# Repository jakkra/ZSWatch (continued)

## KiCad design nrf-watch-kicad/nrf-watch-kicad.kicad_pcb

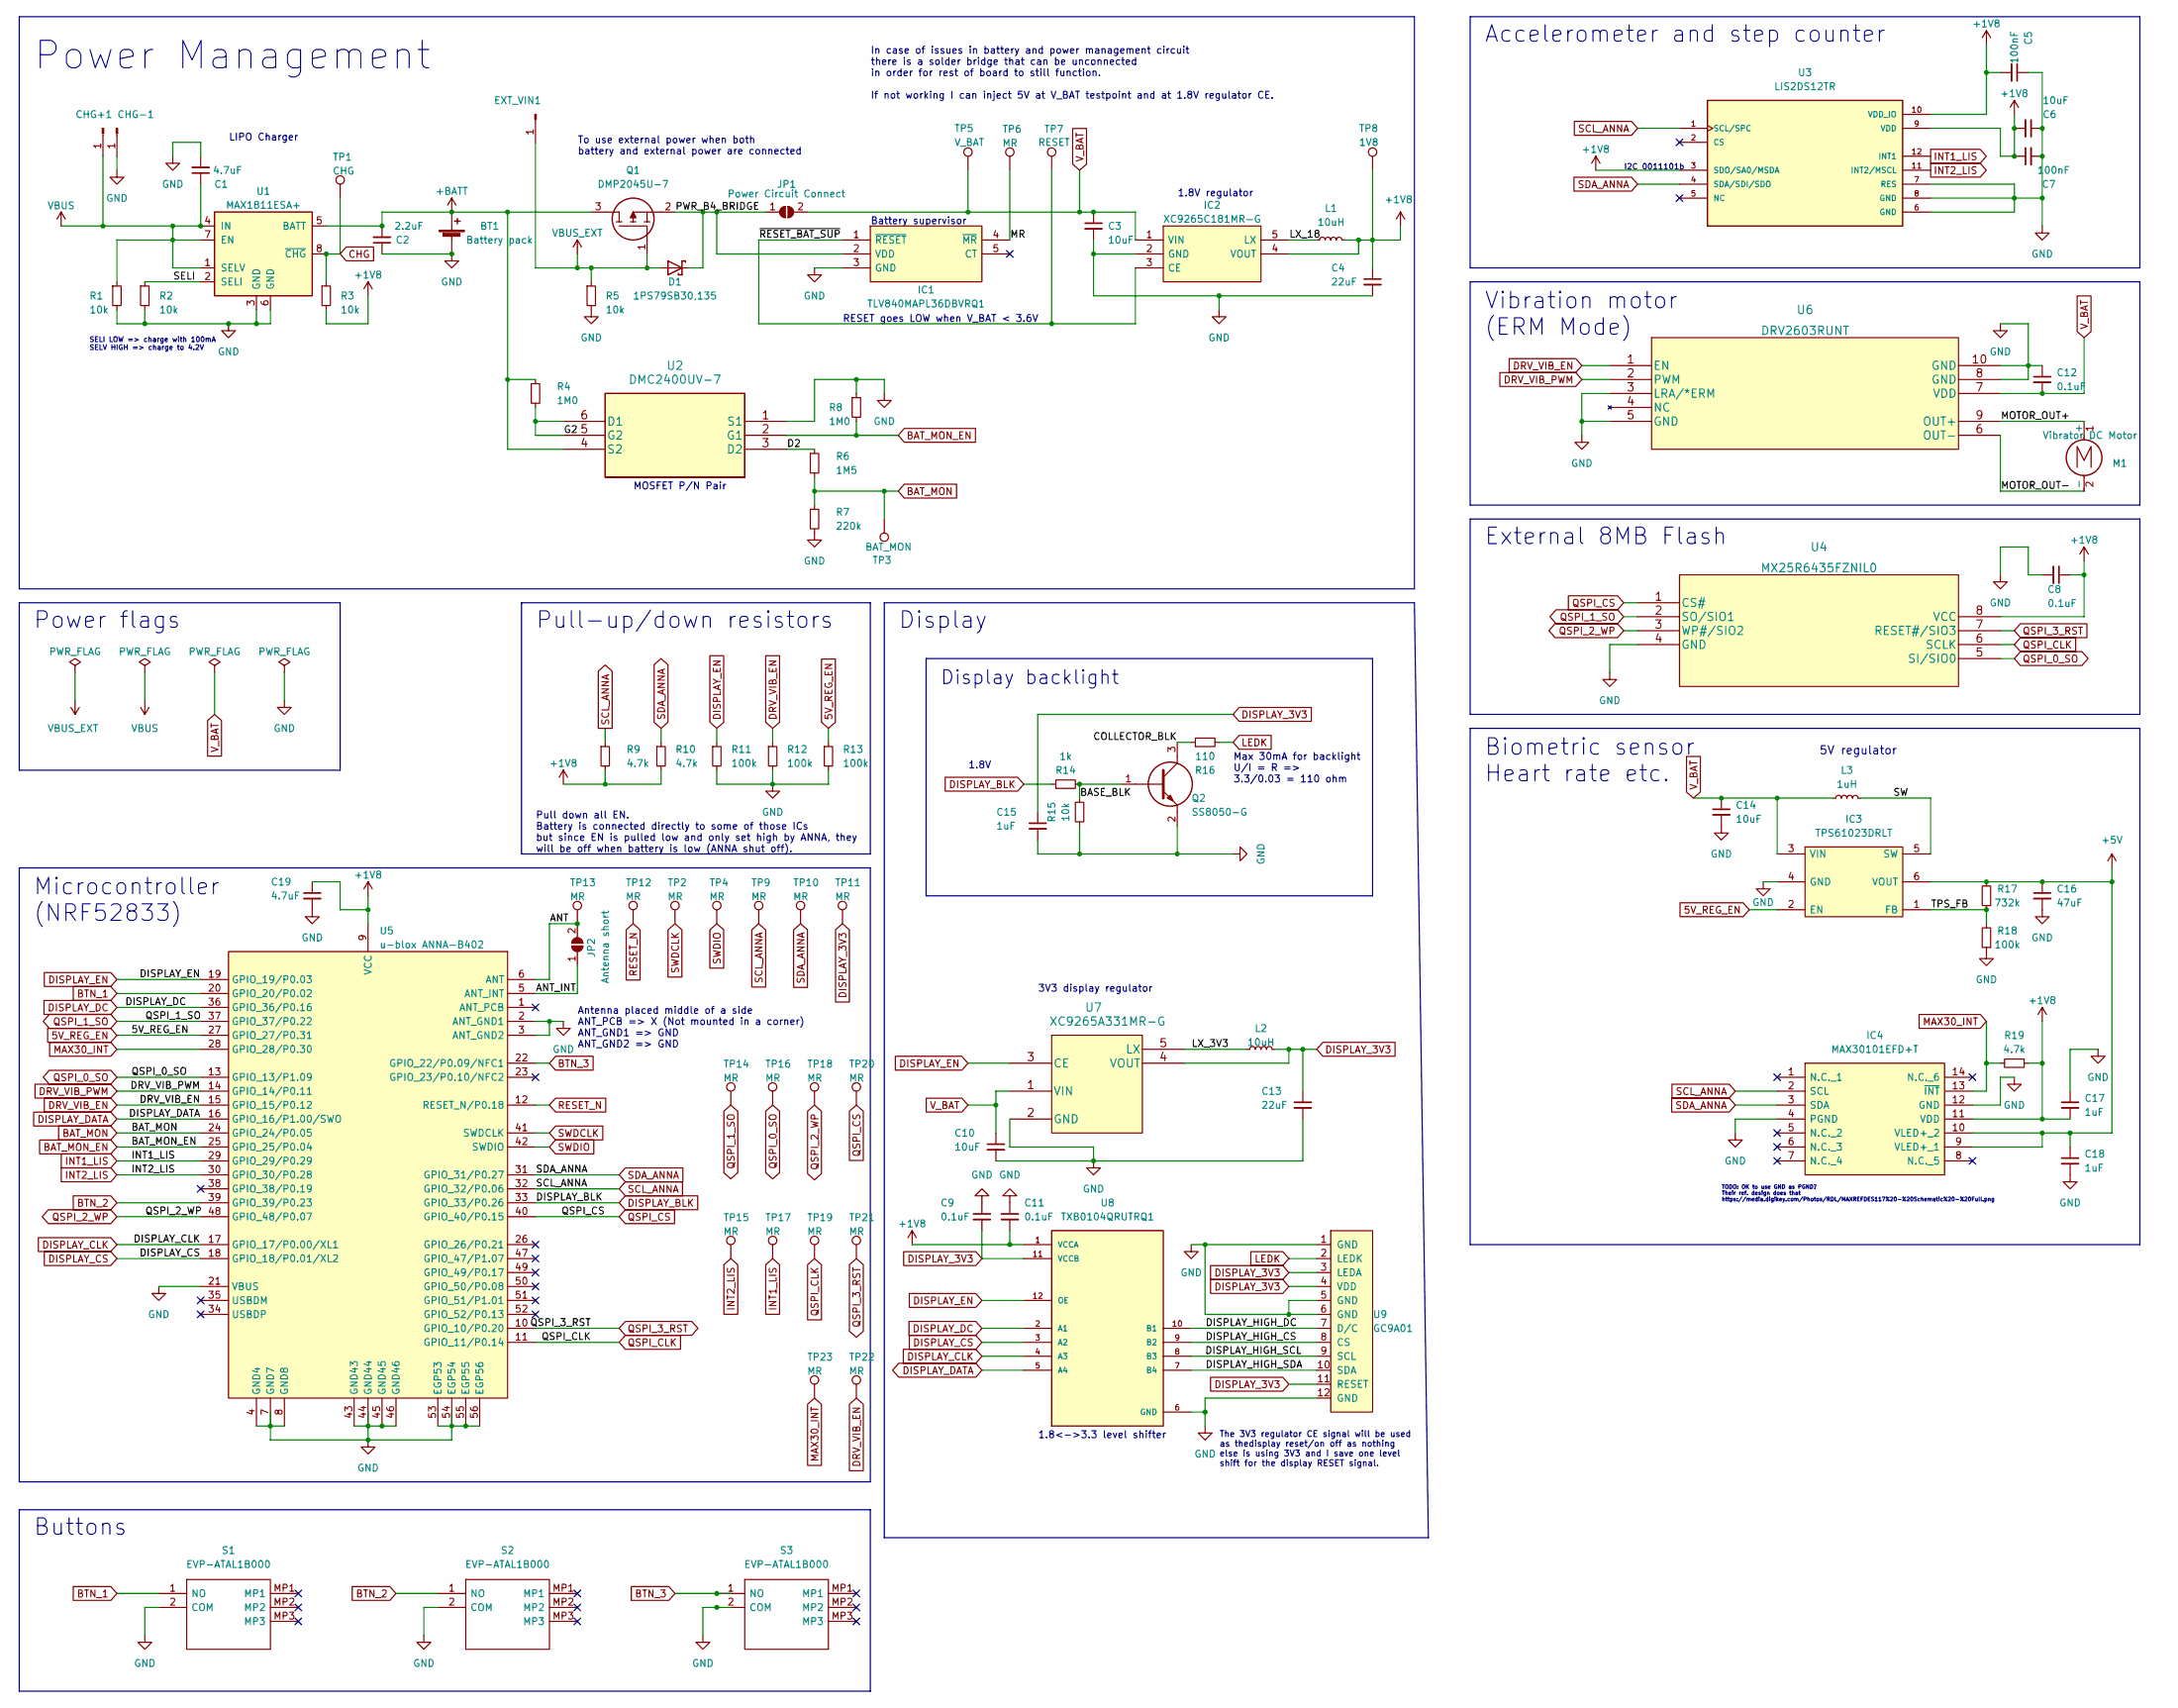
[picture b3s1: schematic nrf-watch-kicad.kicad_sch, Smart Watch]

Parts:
BT1: Battery pack; SolderWire-0.1sqmm_1x02_P3.6mm_D0.4mm_OD1mm
C1, C19: 4.7uF; C_0603_1608Metric_Pad1.08x0.95mm_HandSolder
C2: 2.2uF; C_0603_1608Metric_Pad1.08x0.95mm_HandSolder
C3, C6, C10, C14: 10uF; C_0603_1608Metric_Pad1.08x0.95mm_HandSolder
C4, C13: 22uF; C_0603_1608Metric_Pad1.08x0.95mm_HandSolder
C5, C7: 100nF; C_0603_1608Metric_Pad1.08x0.95mm_HandSolder
C8, C9, C11, C12: 0.1uF; C_0603_1608Metric_Pad1.08x0.95mm_HandSolder
C15, C17, C18: 1uF; C_0603_1608Metric_Pad1.08x0.95mm_HandSolder
C16: 47uF; C_0603_1608Metric_Pad1.08x0.95mm_HandSolder
CHG+1: Conn_01x01_Male; TestPoint_Pad_D1.5mm
CHG-1: Conn_01x01_Male; TestPoint_Pad_1.5x1.5mm
D1: 1PS79SB30,135; SOD523
EXT_VIN1: Conn_01x01_Male; TestPoint_Pad_D1.5mm
IC1: TLV840MAPL36DBVRQ1; SOT95P280X145-5N; Mouser Part Number 595-V840MAPL36DBVRQ1
IC2: XC9265C181MR-G; SOT95P280X130-5N; Mouser Part Number 865-XC9265C181MR-G
IC3: TPS61023DRLT; SOTFL50P160X60-6N; Mouser Part Number 595-TPS61023DRLT
IC4: MAX30101EFD+T; 14-LEAD-OESIP; Mouser Part Number 700-MAX30101EFD+T
JP1: Power Circuit Connect; SolderJumper-2_P1.3mm_Open_RoundedPad1.0x1.5mm
JP2: Antenna short; SolderJumper-2_P1.3mm_Open_Pad1.0x1.5mm
L1, L2: 10uH; L_0603_1608Metric_Pad1.05x0.95mm_HandSolder
L3: 1uH; L_0603_1608Metric_Pad1.05x0.95mm_HandSolder
M1: Vibrator DC Motor; TestPoint_2Pads_Pitch2.54mm_Drill0.8mm
Q1: DMP2045U-7; SOT96P240X110-3N; Mouser Part Number 621-DMP2045U-7
Q2: SS8050-G; SOT95P240X115-3N; Mouser Part Number 750-SS8050-G
R1, R2, R3, R5, R15: 10k; R_0603_1608Metric_Pad0.98x0.95mm_HandSolder
R4, R8: 1M0; R_0603_1608Metric_Pad0.98x0.95mm_HandSolder
R6: 1M5; R_0603_1608Metric_Pad0.98x0.95mm_HandSolder
R7: 220k; R_0603_1608Metric_Pad0.98x0.95mm_HandSolder
R9, R10, R19: 4.7k; R_0603_1608Metric_Pad0.98x0.95mm_HandSolder
R11, R12, R13, R18: 100k; R_0603_1608Metric_Pad0.98x0.95mm_HandSolder
R14: 1k; R_0603_1608Metric_Pad0.98x0.95mm_HandSolder
R16: 110; R_0603_1608Metric_Pad0.98x0.95mm_HandSolder
R17: 732k; R_0603_1608Metric_Pad0.98x0.95mm_HandSolder
S1, S2, S3: EVP-ATAL1B000; EVPATAL1B000; Mouser Part Number 667-EVP-ATAL1B000
TP1: CHG; TestPoint_Pad_D1.0mm
TP2, TP4, TP6, TP9, TP10, TP11, TP12, TP13: MR; TestPoint_Pad_D1.0mm
TP3: BAT_MON; TestPoint_Pad_D1.0mm
TP5: V_BAT; TestPoint_Pad_D1.0mm
TP7: RESET; TestPoint_Pad_D1.0mm
TP8: 1V8; TestPoint_Pad_D1.0mm
TP14, TP15, TP16, TP17, TP18, TP19, TP20, TP21, TP22, TP23: MR; TestPoint_Pad_D0.4mm
U1: MAX1811ESA+; SOIC127P600X175-8N
U2: DMC2400UV-7
U3: LIS2DS12TR
U4: MX25R6435FZNIL0
U5: u-blox ANNA-B402; ANNA-B402_altium_import
U6: DRV2603RUNT
U7: XC9265A331MR-G; SOT95P280X130-5N
U8: TXB0104QRUTRQ1; HPA01164RUTR; PARTREV 4210580/C 06/12
U9: GC9A01; GC9A01_disp

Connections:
5V_REG_EN: IC3.2 (EN), R13.1, U5.27 (GPIO_27/P0.31)
+1V8: C4.1, C5.2, C6.2, C7.1, C8.1, C11.2, C17.2, C19.1, IC2.4 (VOUT), IC4.11 (VDD), L1.2, R3.2, R9.2, R10.2, R19.1, TP8.1, U3.3 (SDO/SA0/MSDA), U3.9 (VDD), U3.10 (VDD_IO), U4.8 (VCC), U5.9 (VCC), U8.1 (VCCA)
+5V: C16.1, C18.1, IC3.6 (VOUT), IC4.9 (VLED+_1), IC4.10 (VLED+_2), R17.2
+BATT: BT1.1 (+), C2.2, Q1.3, R4.1, U1.5 (BATT), U2.4 (S2)
/ANT: JP2.2 (B), TP13.1, U5.6 (ANT)
/ANT_INT: JP2.1 (A), U5.5 (ANT_INT)
/BASE_BLK: Q2.1, R14.2, R15.1
/COLLECTOR_BLK: Q2.3, R16.1
/D2: R6.1, U2.3 (D2)
/DISPLAY_HIGH_CS: U8.9 (B2), U9.8 (CS)
/DISPLAY_HIGH_DC: U8.10 (B1), U9.7 (D/C)
/DISPLAY_HIGH_SCL: U8.8 (B3), U9.9 (SCL)
/DISPLAY_HIGH_SDA: U8.7 (B4), U9.10 (SDA)
/G2: R4.2, U2.5 (G2), U2.6 (D1)
/LX_3V3: L2.1, U7.5 (LX)
/LX_18: IC2.5 (LX), L1.1
/MOTOR_OUT+: M1.1 (+), U6.9 (OUT+)
/MOTOR_OUT-: M1.2 (-), U6.6 (OUT-)
/MR: IC1.4 (~MR), TP6.1
/PWR_B4_BRIDGE: D1.1, IC1.2 (VDD), JP1.1 (A), Q1.2
/SELI: R2.1, U1.2 (SELI)
/SW: IC3.5 (SW), L3.2
/TPS_FB: IC3.1 (FB), R17.1, R18.2
/~RESET_BAT_SUP: IC1.1 (~RESET), IC2.3 (CE), TP7.1
BAT_MON: R6.2, R7.1, TP3.1, U5.24 (GPIO_24/P0.05)
BAT_MON_EN: R8.2, U2.2 (G1), U5.25 (GPIO_25/P0.04)
BTN_1: S1.1 (NO), U5.20 (GPIO_20/P0.02)
BTN_2: S2.1 (NO), U5.39 (GPIO_39/P0.23)
BTN_3: S3.1 (NO), U5.22 (GPIO_22/P0.09/NFC1)
CHG: R3.1, TP1.1, U1.8 (~CHG)
DISPLAY_3V3: C9.2, C13.1, C15.1, L2.2, TP11.1, U7.4 (VOUT), U8.11 (VCCB), U9.3 (LEDA), U9.4 (VDD), U9.11 (RESET)
DISPLAY_BLK: R14.1, U5.33 (GPIO_33/P0.26)
DISPLAY_CLK: U5.17 (GPIO_17/P0.00/XL1), U8.4 (A3)
DISPLAY_CS: U5.18 (GPIO_18/P0.01/XL2), U8.3 (A2)
DISPLAY_DATA: U5.16 (GPIO_16/P1.00/SWO), U8.5 (A4)
DISPLAY_DC: U5.36 (GPIO_36/P0.16), U8.2 (A1)
DISPLAY_EN: R11.1, U5.19 (GPIO_19/P0.03), U7.3 (CE), U8.12 (OE)
DRV_VIB_EN: R12.1, TP22.1, U5.15 (GPIO_15/P0.12), U6.1 (EN)
DRV_VIB_PWM: U5.14 (GPIO_14/P0.11), U6.2 (PWM)
GND: BT1.2 (-), C1.2, C2.1, C3.2, C4.2, C5.1, C6.1, C7.2, C8.2, C9.1, C10.2, C11.1, C12.1, C13.2, C14.2, C15.2, C16.2, C17.1, C18.2, C19.2, CHG-1.1, IC1.3 (GND), IC2.2 (GND), IC3.4 (GND), IC4.4 (PGND), IC4.12 (GND), Q2.2, R1.2, R2.2, R5.2, R7.2, R8.1, R11.2, R12.2, R13.2, R15.2, R18.1, S1.2 (COM), S2.2 (COM), S3.2 (COM), U1.3 (GND), U1.6 (GND), U2.1 (S1), U3.6 (GND), U3.7 (RES), U3.8 (GND), U4.4 (GND), U5.2 (ANT_GND1), U5.3 (ANT_GND2), U5.4 (GND4), U5.7 (GND7), U5.8 (GND8), U5.21 (VBUS), U5.43 (GND43), U5.44 (GND44), U5.45 (GND45), U5.46 (GND46), U5.53 (EGP53), U5.54 (EGP54), U5.55 (EGP55), U5.56 (EGP56), U6.3 (LRA/*ERM), U6.5 (GND), U6.8 (GND), U6.10 (GND), U7.2 (GND), U8.6 (GND), U9.1 (GND), U9.5 (GND), U9.6 (GND), U9.12 (GND)
INT1_LIS: TP17.1, U3.12 (INT1), U5.29 (GPIO_29/P0.29)
INT2_LIS: TP15.1, U3.11 (INT2/MSCL), U5.30 (GPIO_30/P0.28)
LEDK: R16.2, U9.2 (LEDK)
MAX30_INT: IC4.13 (~INT), R19.2, TP23.1, U5.28 (GPIO_28/P0.30)
QSPI_0_SO: TP16.1, U4.5 (SI/SIO0), U5.13 (GPIO_13/P1.09)
QSPI_1_SO: TP14.1, U4.2 (SO/SIO1), U5.37 (GPIO_37/P0.22)
QSPI_2_WP: TP18.1, U4.3 (WP#/SIO2), U5.48 (GPIO_48/P0.07)
QSPI_3_RST: TP21.1, U4.7 (RESET#/SIO3), U5.10 (GPIO_10/P0.20)
QSPI_CLK: TP19.1, U4.6 (SCLK), U5.11 (GPIO_11/P0.14)
QSPI_CS: TP20.1, U4.1 (CS#), U5.40 (GPIO_40/P0.15)
RESET_N: TP12.1, U5.12 (RESET_N/P0.18)
SCL_ANNA: IC4.2 (SCL), R9.1, TP9.1, U3.1 (SCL/SPC), U5.32 (GPIO_32/P0.06)
SDA_ANNA: IC4.3 (SDA), R10.1, TP10.1, U3.4 (SDA/SDI/SDO), U5.31 (GPIO_31/P0.27)
SWDCLK: TP2.1, U5.41 (SWDCLK)
SWDIO: TP4.1, U5.42 (SWDIO)
VBUS: C1.1, CHG+1.1, R1.1, U1.1 (SELV), U1.4 (IN), U1.7 (EN)
VDDA: D1.2, EXT_VIN1.1, Q1.1, R5.1
V_BAT: C3.1, C10.1, C12.2, C14.1, IC2.1 (VIN), IC3.3 (VIN), JP1.2 (B), L3.1, TP5.1, U6.7 (VDD), U7.1 (VIN)

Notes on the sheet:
Display backlight
Biometric sensor Heart rate etc.
Antenna placed middle of a side ANT_PCB => X (Not mounted in a corner) ANT_GND1 => GND ANT_GND2 => GND
Microcontroller (NRF52833)
3V3 display regulator
Pull-up/down resistors
MOSFET P/N Pair
Power Management
SELI LOW => charge with 100mA SELV HIGH => charge to 4.2V
Battery supervisor
RESET goes LOW when V_BAT < 3.6V
Buttons
TODO: OK to use GND as PGND? Their ref. design does that https://media.digikey.com/Photos/RDL/MAXREFDES117%20-%20Schematic%20-%20Full.png
Max 30mA for backlight U/I = R => 3.3/0.03 = 110 ohm
In case of issues in battery and power management circuit there is a solder bridge that can be unconnected in order for rest of board to still function. If not working I can inject 5V at V_BAT testpoint and at 1.8V regulator CE.
Power flags
To use external power when both battery and external power are connected
External 8MB Flash
Pull down all EN. Battery is connected directly to some of those ICs but since EN is pulled low and only set high by ANNA, they will be off when battery is low (ANNA shut off).
Accelerometer and step counter
LIPO Charger
_{I2C 0011101b}
5V regulator
1.8<->3.3 level shifter
The 3V3 regulator CE signal will be used as thedisplay reset/on off as nothing else is using 3V3 and I save one level shift for the display RESET signal.
Vibration motor (ERM Mode)
Display
1.8V regulator
1.8V

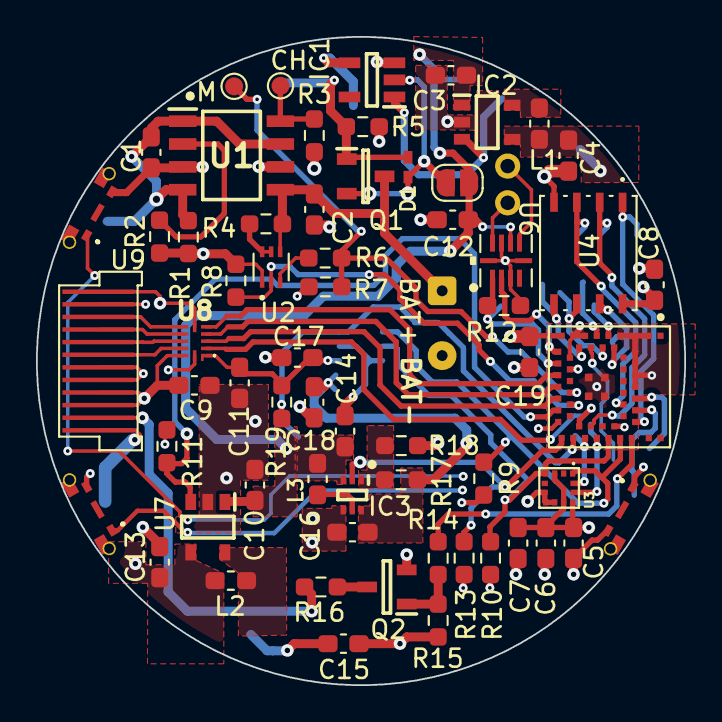
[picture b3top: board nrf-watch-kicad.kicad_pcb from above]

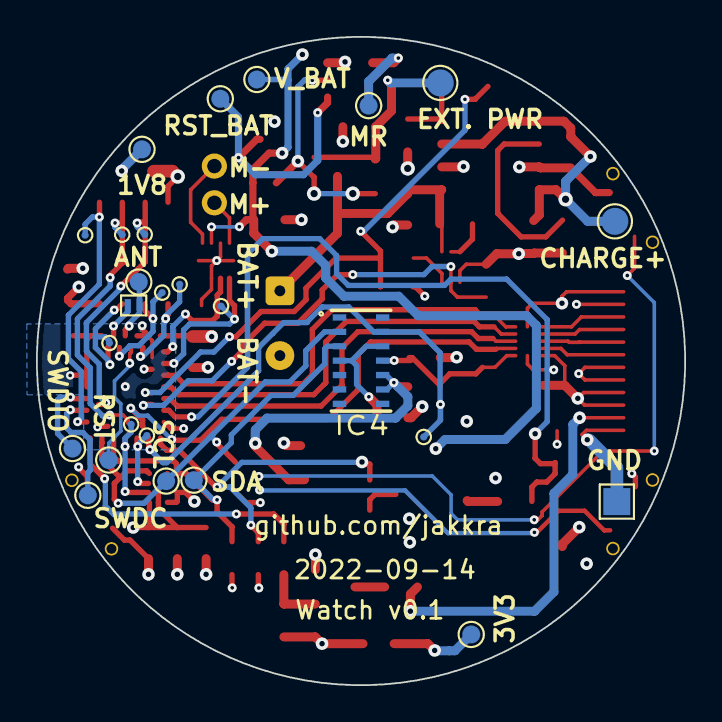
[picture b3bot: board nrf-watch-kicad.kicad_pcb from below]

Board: 4 copper layers, 36.0 x 36.0 mm, 90 parts (26 on the bottom side), 58 nets.

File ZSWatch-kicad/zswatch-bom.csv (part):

Source:,G:\projects\watch\ZSWatch-kicad\nrf-watch-kicad.kicad_sch,,,,,,,,,,,,,,,,,,,,,,,,,
Date:,1/16/2023 8:22:16 AM,,,,,,,,,,,,,,,,,,,,,,,,,
Tool:,Eeschema (6.0.7),,,,,,,,,,,,,,,,,,,,,,,,,
Generator:,G:\Programs\KiCad\6.0\bin\scripting\plugins/bom_csv_grouped_by_value.py,,,,,,,,,,,,,,,,,,,,,,,,,
Component Count:,90,,,,,,,,,,,,,,,,,,,,,,,,,
,,,,,,,,,,,,,,,,,,,,,,,,,,
,,,,,,,,,,,,,,,,,,,,,,,,,,
Collated Components:,,,,,,,,,,,,,,,,,,,,,,,,,,
,,,,,,,,,,,,,,,,,,,,,,,,,,
Item,Qty,Reference(s),Value,LibPart,Footprint,Datasheet,4MB variant,Buy,Description,Ds_opt,Height,MANUFACTURER,MAXIMUM_PACKAGE_HEIGHT,Manufacturer_Name,Manufacturer_Part_Number,Mouser Part Number,Mouser Price/Stock,Option other foot,Options,PARTREV,STANDARD,Type,app note,backlight?,buy,motor
1,1,BT1,Battery pack,Device:Battery_Cell,Connector_Wire:SolderWire-0.1sqmm_1x02_P3.6mm_D0.4mm_OD1mm,~,,,,,,,,,,,,,,,,,,,,
2,2,"C1, C19",4.7uF,Device:C_Small,Capacitor_SMD:C_0603_1608Metric_Pad1.08x0.95mm_HandSolder,~,,,,,,,,,,,,,,,,,,,,
3,1,C2,2.2uF,Device:C_Small,Capacitor_SMD:C_0603_1608Metric_Pad1.08x0.95mm_HandSolder,~,,,,,,,,,,,,,,,,,,,,
4,4,"C3, C6, C10, C14",10uF,Device:C_Small,Capacitor_SMD:C_0603_1608Metric_Pad1.08x0.95mm_HandSolder,~,,,,,,,,,,,,,,,,Ceramic,,,,
5,2,"C4, C13",22uF,Device:C_Small,Capacitor_SMD:C_0603_1608Metric_Pad1.08x0.95mm_HandSolder,~,,,,,,,,,,,,,,,,Ceramic,,,,
6,2,"C5, C7",100nF,Device:C_Small,Capacitor_SMD:C_0603_1608Metric_Pad1.08x0.95mm_HandSolder,~,,,,,,,,,,,,,,,,,,,,
7,4,"C8, C9, C11, C12",0.1uF,Device:C_Small,Capacitor_SMD:C_0603_1608Metric_Pad1.08x0.95mm_HandSolder,~,,,,,,,,,,,,,,,,,,,,
8,3,"C15, C17, C18",1uF,Device:C_Small,Capacitor_SMD:C_0603_1608Metric_Pad1.08x0.95mm_HandSolder,~,,,,,,,,,,,,,,,,,,,,
9,1,C16,47uF,Device:C_Small,Capacitor_SMD:C_0603_1608Metric_Pad1.08x0.95mm_HandSolder,~,,,,,,,,,,,,,,,,,,,,
10,2,"CHG+1, CHG-1",Conn_01x01_Male,Connector:Conn_01x01_Male,TestPoint:TestPoint_THTPad_D1.0mm_Drill0.5mm,~,,,,,,,,,,,,,,,,,,,,
11,1,D1,"1PS79SB30,135","user_library:1PS79SB30,135",user_library:SOD523,https://www.mouser.se/datasheet/2/916/1PS79SB30-1880095.pdf,,,,,,,,,,,,,,,,,,,https://www.digikey.se/en/products/detail/nexperia-usa-inc/1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,
12,1,EXT_VIN1,Conn_01x01_Male,Connector:Conn_01x01_Male,TestPoint:TestPoint_Pad_D1.5mm,~,,,,,,,,,,,,,,,,,,,,
13,1,IC1,TLV840MAPL36DBVRQ1,SamacSys_Parts:TLV840MAPL36DBVRQ1,SamacSys_Parts:SOT95P280X145-5N,https://www.ti.com/lit/gpn/TLV840-Q1,,,Supervisory Circuits Automotive low-voltage supervisor with adjustable-reset time delay and manual reset,,01.45,,,Texas Instruments,TLV840MAPL36DBVRQ1,595-V840MAPL36DBVRQ1,https://www.mouser.co.uk/ProductDetail/Texas-Instruments/TLV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,,,,,,,,,
14,1,IC2,XC9265C181MR-G,SamacSys_Parts:XC9265C181MR-G,SamacSys_Parts:SOT95P280X130-5N,https://www.torexsemi.com/file/xc9265/XC9265.pdf,,,Switching Voltage Regulators Ultra Low Power PFM DCDC Converter,,1.3,,,Torex,XC9265C181MR-G,865-XC9265C181MR-G,https://www.mouser.co.uk/ProductDetail/Torex-Semiconductor/X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,,,,,,,,,
15,1,IC3,TPS61023DRLT,SamacSys_Parts:TPS61023DRLT,SamacSys_Parts:SOTFL50P160X60-6N,http://www.ti.com/general/docs/suppproductinfo.tsp?distId=10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,,,Switching Voltage Regulators 3-A boost converter with 0.5-V ultra-low input voltage 6-SOT-5X3 -40 to 125,,0.6,,,Texas Instruments,TPS61023DRLT,595-TPS61023DRLT,https://www.mouser.co.uk/ProductDetail/Texas-Instruments/TPS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,,,,,,,,,
16,1,IC4,MAX30101EFD+T,SamacSys_Parts:MAX30101EFD+T,SamacSys_Parts:14-LEAD-OESIP,https://datasheets.maximintegrated.com/en/ds/MAX30101.pdf,,,Biometric Sensors Integrated Optical Sensor,,,,,Maxim Integrated,MAX30101EFD+T,700-MAX30101EFD+T,https://www.mouser.co.uk/ProductDetail/Maxim-Integrated/MAX3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,,,,,,https://pdfserv.maximintegrated.com/en/an/AN6409.pdf,,,
17,1,JP1,Power Circuit Connect,Jumper:SolderJumper_2_Open,Jumper:SolderJumper-2_P1.3mm_Open_RoundedPad1.0x1.5mm,~,,,,,,,,,,,,,,,,,,,,
18,1,JP2,Antenna short,Jumper:SolderJumper_2_Open,Jumper:SolderJumper-2_P1.3mm_Open_Pad1.0x1.5mm,~,,,,,,,,,,,,,,,,,,,,
19,2,"L1, L2",10uH,Device:L_Small,Inductor_SMD:L_0603_1608Metric_Pad1.05x0.95mm_HandSolder,~,,,,,,,,,,,,,,,,,,,,
20,1,L3,1uH,Device:L_Small,Inductor_SMD:L_0603_1608Metric_Pad1.05x0.95mm_HandSolder,~,,,,,,,,,,,,,,,,,,,,
21,1,M1,Vibrator DC Motor,Motor:Motor_DC,user_library:TestPoint_2Pads_Pitch2.54mm_Drill0.8mm,~,,,,,,,,,,,,,,,,,,,,
22,1,Q1,DMP2045U-7,SamacSys_Parts:DMP2045U-7,SamacSys_Parts:SOT96P240X110-3N,https://www.diodes.com/assets/Datasheets/DMP2045U.pdf,,,"DMP2045U-7 P-Channel MOSFET, 3.5 (State) A, 4.3 (Steady) A, 20 V, 3-Pin SOT-23 Diodes Inc",,1.1,,,Diodes Inc.,DMP2045U-7,621-DMP2045U-7,https://www.mouser.co.uk/ProductDetail/Diodes-Incorporated/D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,,,,,,,,,
23,1,Q2,SS8050-G,SamacSys_Parts:SS8050-G,SamacSys_Parts:SOT95P240X115-3N,https://datasheet.datasheetarchive.com/originals/distributor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,,,Bipolar Transistors - BJT NPN TRANSISTOR 1.5A 40V,,01.15,,,Comchip Technology,SS8050-G,750-SS8050-G,https://www.mouser.co.uk/ProductDetail/Comchip-Technology/SS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,,,,,,,,,
24,5,"R1, R2, R3, R5, R15",10k,Device:R_Small,Resistor_SMD:R_0603_1608Metric_Pad0.98x0.95mm_HandSolder,~,,,,,,,,,,,,,,,,,,,,
25,2,"R4, R8",1M0,Device:R_Small,Resistor_SMD:R_0603_1608Metric_Pad0.98x0.95mm_HandSolder,~,,,,,,,,,,,,,,,,,,,,
26,1,R6,1M5,Device:R_Small,Resistor_SMD:R_0603_1608Metric_Pad0.98x0.95mm_HandSolder,~,,,,,,,,,,,,,,,,,,,,
27,1,R7,220k,Device:R_Small,Resistor_SMD:R_0603_1608Metric_Pad0.98x0.95mm_HandSolder,~,,,,,,,,,,,,,,,,,,,,
28,3,"R9, R10, R19",4.7k,Device:R_Small,Resistor_SMD:R_0603_1608Metric_Pad0.98x0.95mm_HandSolder,~,,,,,,,,,,,,,,,,,,,,
29,4,"R11, R12, R13, R18",100k,Device:R_Small,Resistor_SMD:R_0603_1608Metric_Pad0.98x0.95mm_HandSolder,~,,,,,,,,,,,,,,,,,,,,
30,1,R14,1k,Device:R_Small,Resistor_SMD:R_0603_1608Metric_Pad0.98x0.95mm_HandSolder,~,,,,,,,,,,,,,,,,,,,,
31,1,R16,110,Device:R_Small,Resistor_SMD:R_0603_1608Metric_Pad0.98x0.95mm_HandSolder,~,,,,,,,,,,,,,,,,,,,,
32,1,R17,732k,Device:R_Small,Resistor_SMD:R_0603_1608Metric_Pad0.98x0.95mm_HandSolder,~,,,,,,,,,,,,,,,,,,,,
33,1,S1,EVP-ATAL1B000,:EVP-ATAL1B000_1,SamacSys_Parts:EVPATAL1B000,https://api.pim.na.industrial.panasonic.com/file_stream/main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,,,Tactile Switches Edge Mount side push 1.6N 4.3x1.7mm,,02.45,,,Panasonic,EVP-ATAL1B000,667-EVP-ATAL1B000,https://www.mouser.co.uk/ProductDetail/Panasonic/EVP-ATAL1B0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,,,,,,,,,
34,1,S2,EVP-ATAL1B000,:EVP-ATAL1B000_2,SamacSys_Parts:EVPATAL1B000,https://api.pim.na.industrial.panasonic.com/file_stream/main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,,,Tactile Switches Edge Mount side push 1.6N 4.3x1.7mm,,02.45,,,Panasonic,EVP-ATAL1B000,667-EVP-ATAL1B000,https://www.mouser.co.uk/ProductDetail/Panasonic/EVP-ATAL1B0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,,,,,,,,,
35,1,S3,EVP-ATAL1B000,SamacSys_Parts:EVP-ATAL1B000,SamacSys_Parts:EVPATAL1B000,https://api.pim.na.industrial.panasonic.com/file_stream/main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,,,Tactile Switches Edge Mount side push 1.6N 4.3x1.7mm,,02.45,,,Panasonic,EVP-ATAL1B000,667-EVP-ATAL1B000,https://www.mouser.co.uk/ProductDetail/Panasonic/EVP-ATAL1B0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,,,,,,,,,
36,1,TP1,CHG,Connector:TestPoint,TestPoint:TestPoint_Pad_D1.0mm,~,,,,,,,,,,,,,,,,,,,,
37,3,"TP2, TP4, TP12",MR,Connector:TestPoint,TestPoint:TestPoint_THTPad_D1.0mm_Drill0.5mm,~,,,,,,,,,,,,,,,,,,,,
38,1,TP3,BAT_MON,Connector:TestPoint,TestPoint:TestPoint_Pad_D1.0mm,~,,,,,,,,,,,,,,,,,,,,
39,1,TP5,V_BAT,Connector:TestPoint,TestPoint:TestPoint_Pad_D1.0mm,~,,,,,,,,,,,,,,,,,,,,
40,5,"TP6, TP9, TP10, TP11, TP13",MR,Connector:TestPoint,TestPoint:TestPoint_Pad_D1.0mm,~,,,,,,,,,,,,,,,,,,,,
41,1,TP7,RESET,Connector:TestPoint,TestPoint:TestPoint_Pad_D1.0mm,~,,,,,,,,,,,,,,,,,,,,
42,1,TP8,1V8,Connector:TestPoint,TestPoint:TestPoint_THTPad_D1.0mm_Drill0.5mm,~,,,,,,,,,,,,,,,,,,,,
43,10,"TP14, TP15, TP16, TP17, TP18, TP19, TP20, TP21, TP22, TP23",MR,Connector:TestPoint,user_library:TestPoint_Pad_D0.4mm,~,,,,,,,,,,,,,,,,,,,,
44,1,U1,MAX1811ESA+,Battery_Management:MAX1811,SamacSys_Parts:SOIC127P600X175-8N,https://datasheets.maximintegrated.com/en/ds/MAX1811.pdf,,https://www.mouser.se/ProductDetail/Maxim-Integrated/MAX1811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,,,,,,,,,,https://www.mouser.se/ProductDetail/Maxim-Integrated/MAX1811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,,,,,,,,
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
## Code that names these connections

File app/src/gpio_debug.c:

#include <zephyr/kernel.h>
#include <zephyr/device.h>
#include <zephyr/sys/__assert.h>
#include <assert.h>
#include <zephyr/drivers/gpio.h>
#include <zephyr/logging/log.h>
#include <gpio_debug.h>

LOG_MODULE_REGISTER(gpio_debug, LOG_LEVEL_WRN);
static struct gpio_dt_spec watch_gpios[] = {
    [TOUCH_RST] = { .port = DEVICE_DT_GET_OR_NULL(DT_NODELABEL(gpio0)), .pin = 20 },
    [TOUCH_SDA] = { .port = DEVICE_DT_GET_OR_NULL(DT_NODELABEL(gpio1)), .pin = 2 },
    [TOUCH_SCL] = { .port = DEVICE_DT_GET_OR_NULL(DT_NODELABEL(gpio1)), .pin = 3 },
    [TOUCH_INT] = { .port = DEVICE_DT_GET_OR_NULL(DT_NODELABEL(gpio1)), .pin = 0 },
    //[DISPLAY_EN] = { .port = DEVICE_DT_GET_OR_NULL(DT_NODELABEL(gpio1)), .pin = 1 },
    //[DISPLAY_RST] = { .port = DEVICE_DT_GET_OR_NULL(DT_NODELABEL(gpio0)), .pin = 23 },
    //[BTN_1] = { .port = DEVICE_DT_GET_OR_NULL(DT_NODELABEL(gpio0)), .pin = 2 },
    //[DISPLAY_DC] = { .port = DEVICE_DT_GET_OR_NULL(DT_NODELABEL(gpio0)), .pin = 16 },
    //[QSPI_1_SO] = { .port = DEVICE_DT_GET_OR_NULL(DT_NODELABEL(gpio0)), .pin = 22 },
    //[V5_REG_EN] = { .port = DEVICE_DT_GET_OR_NULL(DT_NODELABEL(gpio0)), .pin = 31 },
    //[MAX30_INT] = { .port = DEVICE_DT_GET_OR_NULL(DT_NODELABEL(gpio0)), .pin = 30 },
    //[QSPI_0_SO] = { .port = DEVICE_DT_GET_OR_NULL(DT_NODELABEL(gpio1)), .pin = 9 },
    //[DRV_VIB_PWM] = { .port = DEVICE_DT_GET_OR_NULL(DT_NODELABEL(gpio0)), .pin = 11 },
    //[DRV_VIB_EN] = { .port = DEVICE_DT_GET_OR_NULL(DT_NODELABEL(gpio0)), .pin = 12 },
//
    //[DISPLAY_DATA] = { .port = DEVICE_DT_GET_OR_NULL(DT_NODELABEL(gpio1)), .pin = 0 },
    //[BAT_MON] = { .port = DEVICE_DT_GET_OR_NULL(DT_NODELABEL(gpio0)), .pin = 5 },
    //[BAT_MON_EN] = { .port = DEVICE_DT_GET_OR_NULL(DT_NODELABEL(gpio0)), .pin = 4 },
    //[INT1_LIS] = { .port = DEVICE_DT_GET_OR_NULL(DT_NODELABEL(gpio0)), .pin = 29 },
    //[INT2_LIS] = { .port = DEVICE_DT_GET_OR_NULL(DT_NODELABEL(gpio0)), .pin = 28 },
    //[BTN_2] = { .port = DEVICE_DT_GET_OR_NULL(DT_NODELABEL(gpio0)), .pin = 23 },
    //[QSPI_2_WP] = { .port = DEVICE_DT_GET_OR_NULL(DT_NODELABEL(gpio0)), .pin = 7 },
    //[DISPLAY_CLK] = { .port = DEVICE_DT_GET_OR_NULL(DT_NODELABEL(gpio0)), .pin = 0 },
    //[DISPLAY_CS] = { .port = DEVICE_DT_GET_OR_NULL(DT_NODELABEL(gpio0)), .pin = 1 },
//
    //[BTN_3] = { .port = DEVICE_DT_GET_OR_NULL(DT_NODELABEL(gpio0)), .pin = 9},
    //[SDA_ANNA] = { .port = DEVICE_DT_GET_OR_NULL(DT_NODELABEL(gpio0)), .pin = 27 },
    //[SCL_ANNA] = { .port = DEVICE_DT_GET_OR_NULL(DT_NODELABEL(gpio0)), .pin = 6 },
    //[DISPLAY_BLK] = { .port = DEVICE_DT_GET_OR_NULL(DT_NODELABEL(gpio0)), .pin = 26 },
    //[QSPI_CS] = { .port = DEVICE_DT_GET_OR_NULL(DT_NODELABEL(gpio0)), .pin = 15 },
    //[QSPI_3_RST] = { .port = DEVICE_DT_GET_OR_NULL(DT_NODELABEL(gpio0)), .pin = 20 },
    //[QSPI_CLK] = { .port = DEVICE_DT_GET_OR_NULL(DT_NODELABEL(gpio0)), .pin = 14 },
};

static uint8_t pinDefaultState[ARRAY_SIZE(watch_gpios)];

void gpio_debug_init(void)
{
    int ret;
    for (int i = 0; i < ARRAY_SIZE(watch_gpios); i++) {
        __ASSERT(device_is_ready(watch_gpios[i].port), "Error: button device %s is not ready\n",  watch_gpios[i].port->name);
        ret = gpio_pin_configure_dt(&watch_gpios[i], GPIO_OUTPUT);
        __ASSERT_NO_MSG(ret == 0);
        ret = gpio_pin_set_dt(&watch_gpios[i], 0);
        __ASSERT_NO_MSG(ret == 0);
    }
}

static bool check_all_match(gpioWatchId_t skip)
{
    int val;
    bool ret = true;

    for (int i = 0; i < ARRAY_SIZE(watch_gpios); i++) {
        if (i == (int)skip) {
            continue;
        }
        val = gpio_pin_get_dt(&watch_gpios[i]);
        if (val != pinDefaultState[i]) {
            LOG_ERR("Missmatch, pin %d changed value of %d, was %d, expected %d", skip, i, val, pinDefaultState[i]);
            ret = false;
        }
    }
    return ret;
}

void gpio_debug_test_all(void)
{
    int ret;
    bool pass = true;

    // Configure all as input
    for (int i = 0; i < ARRAY_SIZE(watch_gpios); i++) {
        __ASSERT(device_is_ready(watch_gpios[i].port), "Error: button device %s is not ready\n",  watch_gpios[i].port->name);
        ret = gpio_pin_configure_dt(&watch_gpios[i], GPIO_OUTPUT);
        __ASSERT_NO_MSG(ret == 0);
        ret = gpio_pin_set_dt(&watch_gpios[i], 0);
        __ASSERT_NO_MSG(ret == 0);
        k_msleep(10);
        ret = gpio_pin_configure_dt(&watch_gpios[i], GPIO_INPUT | GPIO_PULL_DOWN);
        __ASSERT_NO_MSG(ret == 0);
    }
    k_msleep(1000);
    for (int i = 0; i < ARRAY_SIZE(watch_gpios); i++) {
        int val = gpio_pin_get_dt(&watch_gpios[i]);
        printk("%d => %d\n", i, val);
        pinDefaultState[i] = val;
        k_msleep(10);
    }

    for (int i = 0; i < ARRAY_SIZE(watch_gpios); i++) {
        printk("Check: %d\n", i);
        k_msleep(250);
        ret = gpio_pin_configure_dt(&watch_gpios[i], GPIO_OUTPUT);
        __ASSERT_NO_MSG(ret == 0);
        ret = gpio_pin_set_dt(&watch_gpios[i], 1);
        __ASSERT_NO_MSG(ret == 0);
        k_msleep(250);
        ret = check_all_match(i);
        if (!ret) {
            pass = false;
            printk("Short detected for %d", i);
        }
        ret = gpio_pin_set_dt(&watch_gpios[i], 0);
        __ASSERT_NO_MSG(ret == 0);
        ret = gpio_pin_configure_dt(&watch_gpios[i], GPIO_INPUT | GPIO_PULL_DOWN);
        __ASSERT_NO_MSG(ret == 0);
        k_msleep(250);
    }

    if (pass) {
        printk("No shorts detected!");
    } else {
        printk("Shorts detected!");
    }
}

void gpio_debug_test(gpioWatchId_t gpioId, int val)
{
    LOG_INF("Testing %d (%s.%d)", gpioId, watch_gpios[gpioId].port->name, watch_gpios[gpioId].pin);
    int ret = gpio_pin_configure_dt(&watch_gpios[gpioId], GPIO_OUTPUT);
    __ASSERT_NO_MSG(ret == 0);

    ret = gpio_pin_set_dt(&watch_gpios[gpioId], val);
    __ASSERT_NO_MSG(ret == 0);
}

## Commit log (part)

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2025-08-21 update app: Support USB disable and building for native_sim to simplify UI development.
2025-08-21 Boards: Remove nPM1300 DK overlay for nRF5340DK.
    Not needed anymore.
2025-08-21 Boards: Remove native_posix board is it's depricated and nativ_sim works well.
2025-08-21 Boards: Group features behind Kconfig to clean up conf files.
2025-08-21 Boards: Align boards with upstream Zephyr Boards allowing some cleanup.
2025-08-21 Remove PCB version config, not needed anymore.
2025-08-21 website: docs: Describe how to add new image resources.
2025-08-25 Website: docs: Fix #427 document last known good VSCode nRF Connect Plugin version.
2025-08-28 ci: Allow tests to run on local runner both for internal and PRs from forks.
    Dual trigger (pull_request, pull_request_target) approach is needed because:
    - Self-hosted runners with hardware are required for testing
    - Fork PRs can't access self-hosted runners with 'pull_request' trigger
    - Fork PRs need 'pull_request_target' for self-hosted runner access and test annotation.
    - Internal PRs need 'pull_request' to test updated workflow files
    - Both triggers have comment/annotation permissions in their respective contexts
2025-08-29 boards: watchdk: Fix wrong name of display power.
    Caused display power never being turned off.
2025-09-03 Fix README banner
2025-09-05 Patch to fix NCS 3.1 bug pins XL1 and XL2 not useable as GPIO.
2025-09-11 mic app: Add FFT spectrum bars of realtime audio.
2025-09-11 Add emulated mic driver for native_sim.
2025-09-18 Fix wrong naming of button node on new boards cuasing rotation overlay build error.
2025-09-18 native_sim: Remove workaround for SDL threading rendering issue on posix.
    This is now fixed in current used Zephyr version.
2025-09-22 Production test: Create separate app for production testing. (#447)
    Reusing as much as possible from the main ZSWatch application.
    west build --build-dir production_test/build production_test --board watchdk@1/nrf5340/cpuapp
    west build --build-dir production_test/build_native production_test --pristine --board native_sim/native/64
2025-09-23 Production: Show countdown until next page on test summary page.
2025-09-25 Calculator App: Add a calculator application based on Zephyr's SMF calculator sample.
2025-09-26 native_sim: Draw a circle illustrating watch screen on all pages.
    This helps with UI work as it's now easier to see where the round watch display edge is.
2025-09-26 Add manager for XIP enable/disable.
    This is a preparation for managing XIP as we need to disable it to decrease current consumption.
2025-09-26 Adjust heaps as weather JSON parsing needs a bit more heap. LVGL will be fine with less.
2025-09-26 Remove app logic files from XIP as they need to work with XIP disabled.
    Only move application UI files to XIP.
2025-09-27 Update hardware project to the latest releases
2025-10-01 website: Add serial firmware update support via WebSerial API.
    Now updating firmware over MCUBoot in addition to BLE works.
    This allows anyone to recover a watch with broken firmware by
    entering MCUBoot and do a serial recovery firmware update.
2025-10-05 display: Add function to stop rendering.
    This is needed when we are modifying the external filesystem with image resources in.
    E.g. when we upload new images.
2025-10-05 custom_fs: Add a trailer to the image to identify if unseuccesful transfer of the image.
    Having a half uploaded custom filesystem image can cause UI issues, so better not use any external
    image if the trailer is missing or incorrect.
2025-10-05 app_manager: Fix app picker cut text when icon not found.
    Fixed by setting a fixed height if the icon is not found.
2025-10-05 Scripts code formatted.
2025-10-09 tests: Reset devices before each test runs.
2025-10-09 mcuboot: Support entering boot from application.
2025-10-09 tests: Add firmware to be used for FW update tests.
    Can't be the same FW that is tested as then images will have
    the same cash and mcuboot will reject us from trying to confrim
    the images as it think we are trying to confirm the already
    running and confirmed images.
2025-10-09 zsw_shell: Expose various zsw api to shell commands.
    Add a zsw_shell.c that takes different parts of zsw that makes sense
    and exposes those APIs externally through shell.
2025-10-14 website: blog: Write blogpost for October.
2025-10-14 ci: Try fix BT HCI error (Authentication Failed)
    Try adding some delay to see if it fixes it.
    Sometimes the test computer BT fails like this:
    "hci0 Set Powered complete, settings: ssp br/edr le secure-conn
    Set Powered for hci0 failed with status 0x05 (Authentication Failed)
2025-10-15 ci: Try fixing BT Adapter hanging in local runner.
2025-10-15 LVGL Editor: Integrate a way to crate App using new LVGL XML Editor.
2025-10-16 ci: Avoid concurrent uses of local runner.
2025-10-23 Optimize flash by disabling not needed functions. Saves about 60KB.
2025-10-24 zsw_history: Fix wrong saved length after data wrap.
    Checking write_index is not correct, in case of wrap we need to save whole buffer.
2025-11-20 Change DK for tests.
2025-11-20 Fix hardware submodule patchs.
2025-11-21 Fix all compile warnings.
2025-11-24 pmic: Fetch the current negotiated USB current.
2025-11-24 Power Debug App: Add a seperate firmware for power consumption debugging.
2025-11-24 cst816: Add power management with auto sleep mode.
    This saves about 1mA when we use the auto wakeup.
2025-11-24 ci: Use hciconfig due to bug in btmgmt when using othert than hci0.
    Because of a bug in btmgmt, --index is ignored in non-interactive mode, so the command always uses hci0.
2025-11-24 Utilize CST816/touch power managment.
    Decreases significantly the worn but display off state from 1.2mA to around 200uA.
2025-11-24 tests: PPK2 is connected to battery in. Measure current consumption of whole watch.
2025-11-24 v5: Disable BME680 as driver don't support low power. It's dropped in new HW anyway.
2025-11-26 zsw_power_manager: Cleanup in tilt code.
2025-11-26 Fix crash when XIP was disabled before USB.
    Reason is the usb_disable is async. hence we can't disable XIP until later.
    There was no suitable callback found, so just use a delay.
2025-11-26 website: Allow dragging in filsystem file without being connected.
2025-11-26 settings app: Remove restart of display.
    Not needed and used
2025-11-26 west coredump: Option to extract from UART instead of RTT.
2025-11-28 Add dummy HR data to watchdk. Send more extensive activity data to Gadgetbridge.
    In preparation for real HR HW we simulate it, in order to work on tools around zswatch.
2025-11-28 zsw_phone_app_publisher: Cleanup some naming.
2025-11-28 Add new BLE Logging backend. Send logs over NUS but encapsulated in <BLELOG>the_log</BLELOG> so it can be differentiated from other data sent.
2025-11-30 zsw_gatt_sensor_server: Add IMU quaternion service (sensor fusion).
2025-12-01 zsw_custom_fs: Use stream_flash API for aligned flash writes
    Some MCUmgr implementations send writes that are not 4-byte aligned.
    So when trying to fix this in the current code, I found that Zephyr
    already has a stream_flash API that handles unaligned writes, buffering,
    and erase-before-write.
    Which means we can clean up our code quite a bit by using that API
    The stream_flash API handles:
2025-12-03 Make cleanup job more compact and remove docker commands
2025-12-03 Revert "ble: add pop up for pairing request"
    This reverts commit 4199d2fd29ba4a74f9a9add92c243b2576e4324b.
2025-12-04 ci: Copy the QSPI Ini file to fw images output.
    Useful when flashing images using command line tools.
2025-12-04 settings_app: Fix crash in settings app.
2025-12-08 gatt_sensor_server: Only send sensor data in explicit cccd enable.
    If we are bonded then CCCD value will be restored on connect, but we don't want to
    start sampling sensors and send that data unless remote explicitly requested it
    for this connection.
2025-12-08 ci: Use more size oprimized container.
2025-12-10 website: blog: Devkit, HR, apps, UI etc.
2025-12-11 Add modified touch driver as module instead of using a patch Add patch to remove upstream touch driver from Zephyr
2025-12-11 Replace debug log with app log in mic manager
2025-12-11 Move UI controller into UI directory and add a separate log level for it
2025-12-11 Change default log level to warning
2025-12-11 Add license text
2025-12-11 Include path simplification, move sensor fusion into sensor driver directory
2025-12-11 Move back sensor fusion Remove double MCUMGR selection entry
2025-12-11 Fix CI/CD issues
2026-01-21 Fix LVGL warning received when rendering sometimes.
2026-02-06 docs: Add getting started for WatchDK.
2026-02-10 Add GitHub Copilot instructions files.
2026-02-11 website: docs: Add a lot of new documentation.
2026-02-12 website: Fix FW image name overflowing update page.
2026-02-12 Update to nRF Connect v3.3-preview1.
2026-02-12 Change to softdevice controller due to data loss with open source controller.
    During FW update and Filesystem update using
    open source LL Controller we get:
    <wrn> bt_hci_core: Unexpected HOST_NUM_COMPLETED_PACKETS, status 0x12
    I have not managed to find out why or a workaround. It works with Softdevice Controller
    so let's use that for now.
2026-02-14 settings: Introduce factory reset.
2026-02-14 copilot instructions: document image bin conversion and add FS image parser.
2026-02-14 ui: Guard app manager transition and onboarding state
2026-02-14 Fix brightness getting set to default value when no setting.
    Also propogate brightness propely to dropdown.
2026-02-14 ui: Add onboarding screen for first boot experience.
2026-02-14 battery_app: Display readable charger status and errors
2026-02-14 tests: clear mcuboot secondary slots before debugger flash
    When tests reflash via nrfjprog, stale DFU images can remain in external
    QSPI secondary slots. MCUboot may then detect those images and swap them
    into primary on next boot, causing mismatched app/XIP images and boot faults.
    Fix by erasing only watchdk MCUboot secondary slot ranges (image 0/1/2) before flashing.
    This preventing unintended MCUboot swaps after restore_firmware.
2026-02-14 native_sim: Fix wrong color format after nRF Connect 3.3 update.
2026-02-18 ci: Add workflow to anaylze PR for needed documentation updates.
2026-02-22 Fix crash in smp code that will run even if SMP is disabled.
    Causing a crash when XIP is off.
2026-02-27 website: Write new Blog Post about Ordering and LLEXT Experiments.
2026-03-02 ci: Run docs PR analyzer on all PRs.
2026-03-03 website: docs: Document filesystem upload using nrfjprog.
2026-03-03 2048 app: Create patch to make it work on our LVGL version.
2026-03-06 Remove nRF5340DK target.
    It does not work anymore and requires quite a bit of work to get up,
    we have the ZSWatch DK also now.
2026-03-10 website: WatchDK Quirks.
2026-03-12 boards: watchdk: Charge battery to 4.2V for better LiPo Compatability.
2026-03-12 Bump firmware version.
2026-03-12 website: note battery estimate accuracy on WatchDK
2026-03-20 Voice Memo recording app and infrastructure.
2026-03-20 testing: Allow better shell testability.
2026-04-02 Docs: Update documentation for #553
    Updated documentation to reflect voice memo feature changes
2026-04-17 ci: Build production test for zswatch board.
